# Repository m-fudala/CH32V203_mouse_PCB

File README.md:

# CH32V203 mouse PCB
A board containing CH32V203 chip that makes use of its supplied USB controller.
On-board button and an LED can be used to perform various HID macros.

 \

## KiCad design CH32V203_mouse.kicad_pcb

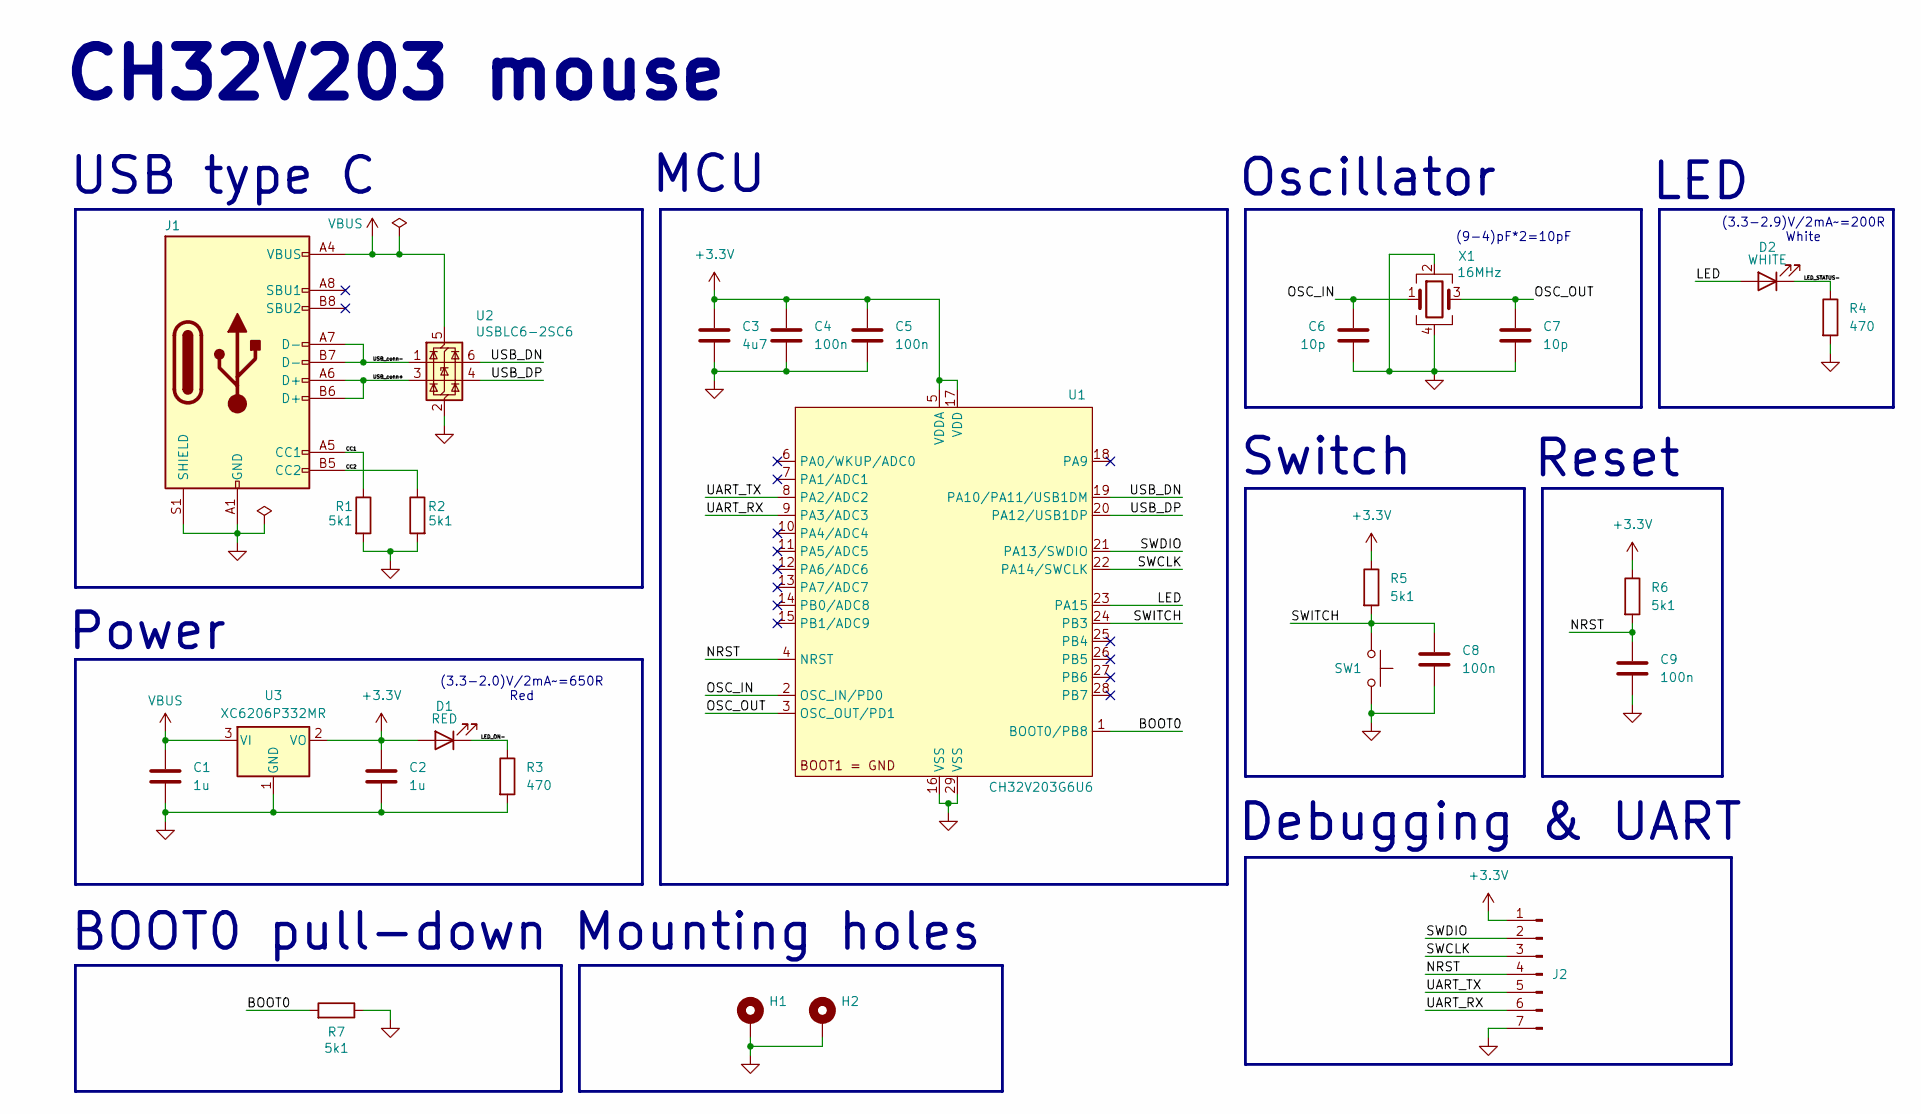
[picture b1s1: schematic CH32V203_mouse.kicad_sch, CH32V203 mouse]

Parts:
C1, C2: 1u; C_0603_1608Metric_Pad1.08x0.95mm_HandSolder; JLCPCB Part # C15849
C3: 4u7; C_0603_1608Metric_Pad1.08x0.95mm_HandSolder; JLCPCB Part # C19666
C4, C5, C8, C9: 100n; C_0402_1005Metric; JLCPCB Part # C1525
C6, C7: 10p; C_0402_1005Metric; JLCPCB Part # C32949
D1: RED; LED_0603_1608Metric; JLCPCB Part # C2286
D2: WHITE; LED_0603_1608Metric; JLCPCB Part # C2290
H1, H2: MountingHole_Pad; MountingHole_2.2mm_M2_DIN965_Pad
J1: USB_C_Receptacle_USB2.0_16P_updated; USB_C_Receptacle_Palconn_UTC16-G; JLCPCB Part # C2927038
J2: Conn_01x07_Pin; JST_ZH_B7B-ZR_1x07_P1.50mm_Vertical
R1, R2, R5, R6, R7: 5k1; R_0402_1005Metric; JLCPCB Part # C25905
R3, R4: 470; R_0402_1005Metric; JLCPCB Part # C25117
SW1: SW_Push; SW_PUSH_6mm_H4.3mm
U1: CH32V203G6U6; QFN-28-1EP_4x4mm_P0.4mm_EP2.8x2.8mm; JLCPCB Part # C5142280
U2: USBLC6-2SC6; SOT-23-6; JLCPCB Part # C5180279
U3: XC6206P332MR; SOT-23-3; JLCPCB Part # C5446
X1: 16MHz; Crystal_SMD_3225-4Pin_3.2x2.5mm; JLCPCB Part # C13738

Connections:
+3.3V: C2.1, C3.1, C4.1, C5.1, D1.2 (A), J2.1, R5.1, R6.1, U1.5 (VDDA), U1.17 (VDD), U3.2 (VO)
/BOOT0: R7.2, U1.1 (BOOT0/PB8)
/CC1: J1.A5 (CC1), R1.1
/CC2: J1.B5 (CC2), R2.1
/LED: D2.2 (A), U1.23 (PA15)
/LED_ON-: D1.1 (K), R3.1
/LED_STATUS-: D2.1 (K), R4.1
/NRST: C9.1, J2.4, R6.2, U1.4 (NRST)
/OSC_IN: C6.1, U1.2 (OSC_IN/PD0), X1.1
/OSC_OUT: C7.1, U1.3 (OSC_OUT/PD1), X1.3
/SWCLK: J2.3, U1.22 (PA14/SWCLK)
/SWDIO: J2.2, U1.21 (PA13/SWDIO)
/SWITCH: C8.1, R5.2, SW1.1, U1.24 (PB3)
/UART_RX: J2.6, U1.9 (PA3/ADC3)
/UART_TX: J2.5, U1.8 (PA2/ADC2)
/USB_DN: U1.19 (PA10/PA11/USB1DM), U2.6 (I/O1)
/USB_DP: U1.20 (PA12/USB1DP), U2.4 (I/O2)
/USB_conn+: J1.A6 (D+), J1.B6 (D+), U2.3 (I/O2)
/USB_conn-: J1.A7 (D-), J1.B7 (D-), U2.1 (I/O1)
GND: C1.2, C2.2, C3.2, C4.2, C5.2, C6.2, C7.2, C8.2, C9.2, H1.1, H2.1, J1.A1 (GND), J1.A12 (GND), J1.B1 (GND), J1.B12 (GND), J1.S1 (SHIELD), J2.7, R1.2, R2.2, R3.2, R4.2, R7.1, SW1.2, U1.16 (VSS), U1.29 (VSS), U2.2 (GND), U3.1 (GND), X1.2, X1.4
VBUS: C1.1, J1.A4 (VBUS), J1.A9 (VBUS), J1.B4 (VBUS), J1.B9 (VBUS), U2.5 (VBUS), U3.3 (VI)

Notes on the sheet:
Switch
Debugging & UART
LED
BOOT0 pull-down
USB type C
(9-4)pF*2=10pF
(3.3-2.0)V/2mA~=650R Red
Reset
(3.3-2.9)V/2mA~=200R White
MCU
Oscillator
Mounting holes
Power
CH32V203 mouse

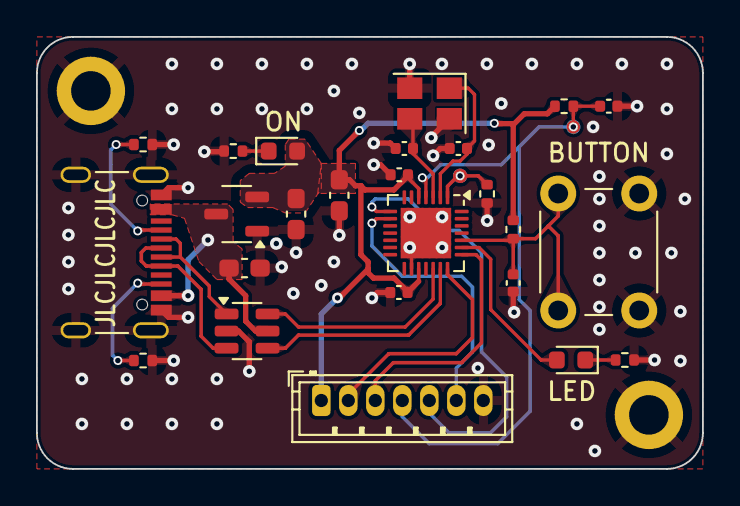
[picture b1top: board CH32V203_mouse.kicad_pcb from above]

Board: 4 copper layers, 37.0 x 24.0 mm, 27 parts (0 on the bottom side), 21 nets.

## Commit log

2024-10-28 Init repo
2024-10-28 MCU placed decoupling capacitors labels added
2024-10-29 3V3 supply using an LDO
2024-10-29 USB type C receptacle, ESD protection ON LED current changed to 2mA, 330R resistor selected net labels
2024-10-29 Crystal oscillator circuit
2024-10-29 Status LED placed changed color of power on LED to red
2024-10-29 Switch circuit reset circuit debugging and UART connectors mounting holes
2024-10-29 BOOT0 pull-down missing power flags
2024-10-29 Footprints selected
2024-10-30 Rough PCB layout
2024-10-30 Better PCB layout decoupling capacitors fixed changed LEDs footprints to correct ones
2024-11-04 Changed stack up to a 4-layer board
2024-11-04 Signals routed Constraints updated USB labels fixed
2024-11-04 Power routing GND vias
2024-11-04 Board outline set missing 3D files added
2024-11-04 GND pours on inner layers fixed DRC violations
2024-11-04 Shifted all components so USB connector overhangs correctly
2024-11-04 Bare copper points for BOOT0 and NRST BOOT0 resistor relocated silkscreen added
2024-11-04 Stitching vias teardrops
2024-11-06 Final touches making sure fabrication files are compatible with JLCPCB
2024-12-15 Added description
2025-04-07 Consolidated debugging and UART connectors and assigned them JST footprint reduced mounting holes' count to two and size to M2
2025-04-07 Decreased connector's size
2025-04-07 Tracks routed to the new connector
2025-04-09 Rerouted tracks
2025-04-09 PCB finished some parts excluded from BOM copper pours on top and bottom layers stitching vias
2025-04-09 Refilled top copper pour with thermal reliefs
